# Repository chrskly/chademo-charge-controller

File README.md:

# CHAdeMO Implementation

This repo contains a car-side implementation of the CHAdeMO EV charging
standard including both the hardware and firmware.

## Features

* Supports CHAdeMO protocols v0.9, v1.0, and v2.0.
* Automatic sleep, wake on plug insertion.
* Separate manual wake button option.

## Chademo Plug Pinout

 1. Ground
 2. CP : evse => car, IN1, contactor +ve signal, goes high when active, sensed by 'f'
 3. nc
 4. CP3 : car => evse, OUT1, charge enable, sensed by 'k'
 5. HV-
 6. HV+
 7. CS : connection check, goes low when plug inserted, sensed by 'h'
 8. CAN H
 9. CAN L
10. CP2 : evse => car, IN2, contactor -ve signal, goes low when active, sensed by 'g'

OUT2, contactor override, pull low to allow CP2 signal through

## Charging start sequence

1. Car pulls CP high (12V) through R3 (1kΩ) when plug is inserted
2. User presses start button on station
3. Station pulls CP high (IN1), d1 closes, +ve contactor closes
4. Car and station start sending CAN messages
5. Car and station check each others params for compatability
6. Car pulls CP3 low and sets CAN vehicleChargingEnabled flag to true to
   indicate it is ready to go ahead with charging
7. Station locks plug to vehicle
8. Station performs insulation test
9. Station pulls CP2 low (IN2), d2 closes, -v3 contactor closes
10. Car ramps up current request. Energy transfer begins.

## Charging stop sequence

1. Car stops pulling CP3 low and sets CAN vehicleChargingEnabled to false.
2. Station deactivates CP and CP2
3. Station unlocks plug

## Questions

- [ ] When to use vehicleChargingEnabled and when to use vehicleRequestingStop?

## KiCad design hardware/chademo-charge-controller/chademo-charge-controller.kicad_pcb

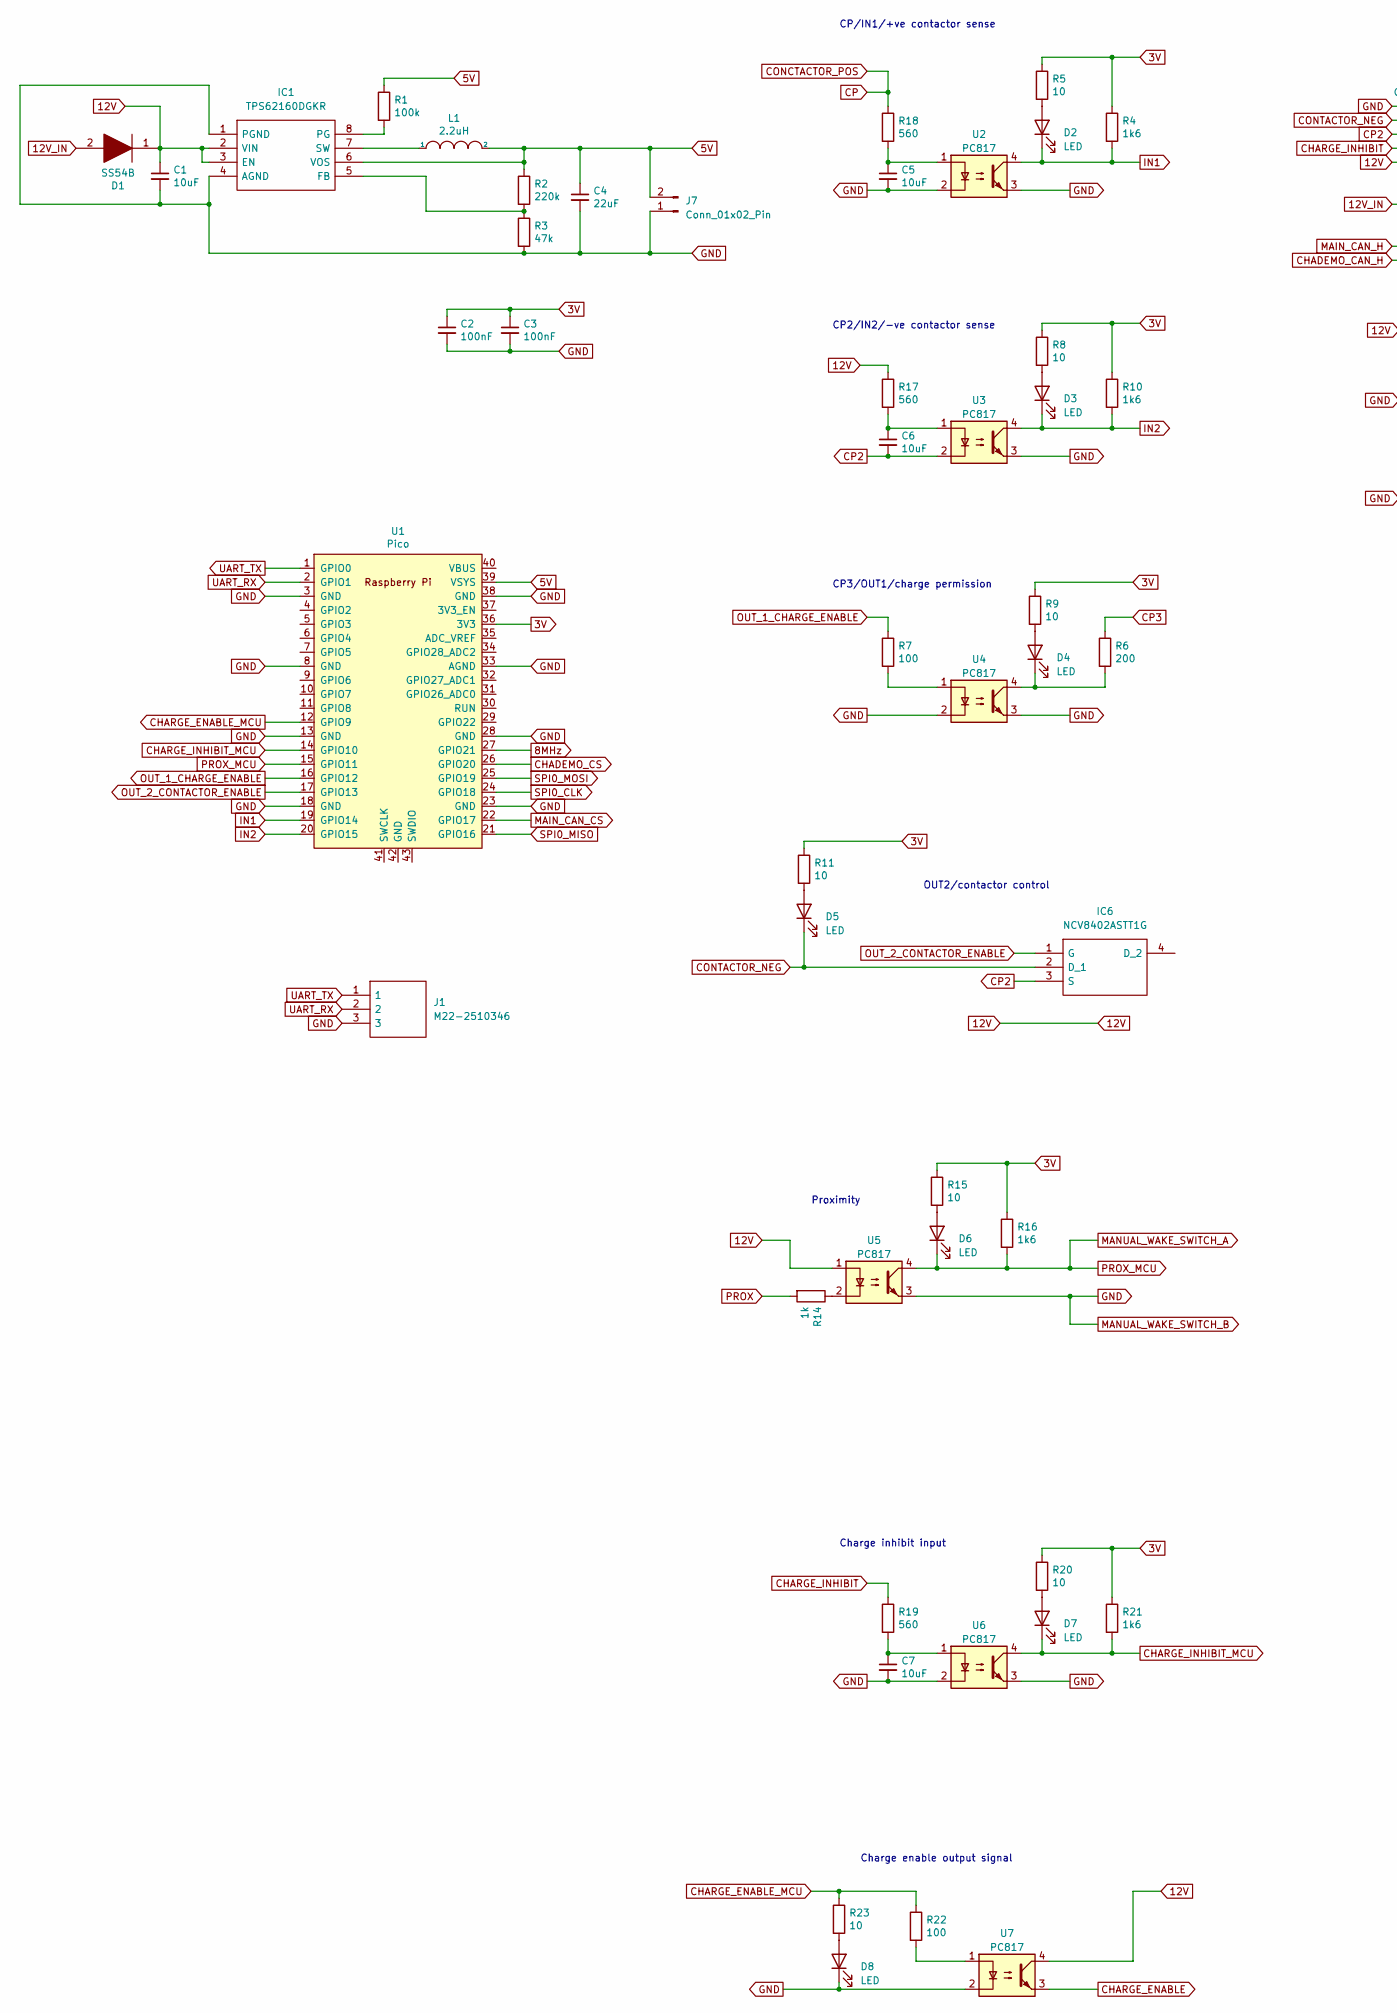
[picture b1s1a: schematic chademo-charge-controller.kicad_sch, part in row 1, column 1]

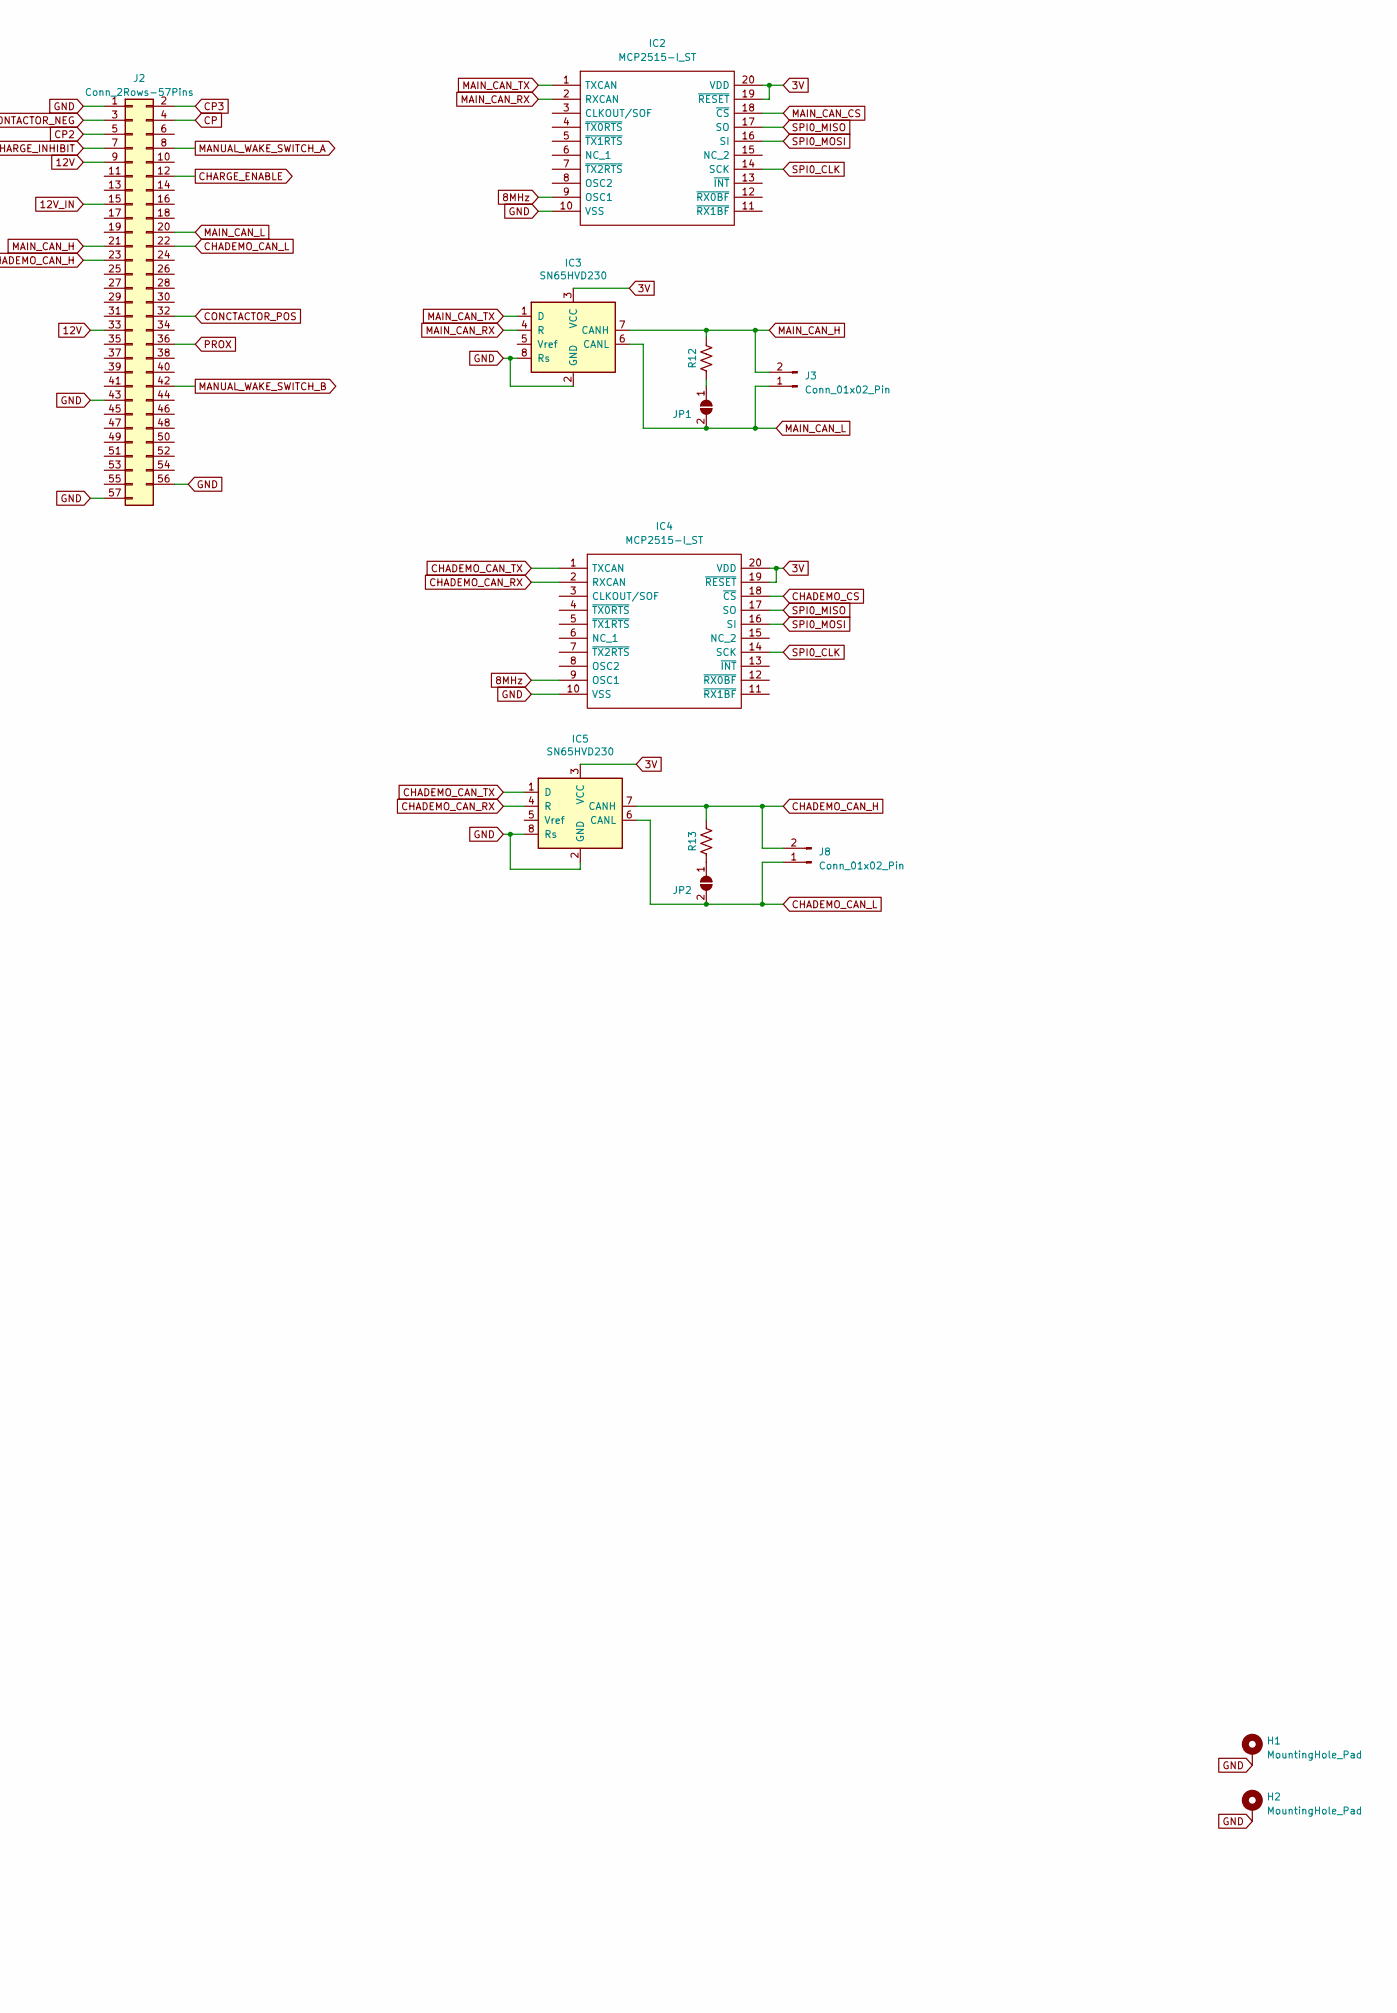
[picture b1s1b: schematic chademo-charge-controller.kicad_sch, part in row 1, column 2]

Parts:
C1, C5, C6, C7: 10uF; C_0603_1608Metric
C2, C3: 100nF; C_0603_1608Metric
C4: 22uF; C_0805_2012Metric
D1: SS54B; DIOM5336X244N; Manufacturer_Part_Number SS54B
D2, D3, D4, D5, D6, D7, D8: LED; LED_0805_2012Metric
H1, H2: MountingHole_Pad; MountingHole_3.2mm_M3_DIN965_Pad
IC1: TPS62160DGKR; SOP65P490X110-8N; Manufacturer_Part_Number TPS62160DGKR; Mouser Part Number 595-TPS62160DGKR
IC2, IC4: MCP2515-I_ST; SOP65P640X120-20N; Manufacturer_Part_Number MCP2515-I/ST
IC3, IC5: SN65HVD230; SOIC-8_3.9x4.9mm_P1.27mm
IC6: NCV8402ASTT1G; SOT230P700X175-4N; Manufacturer_Part_Number NCV8402ASTT1G; Mouser Part Number 863-NCV8402ASTT1G
J1: M22-2510346; PinHeader_1x03_P2.54mm_Horizontal; Manufacturer_Part_Number M22-2510346; Mouser Part Number 855-M22-2510346
J2: Conn_2Rows-57Pins; delphi56
J3, J7, J8: Conn_01x02_Pin; PinHeader_1x02_P2.54mm_Vertical
JP1, JP2: SolderJumper_2_Open; SolderJumper-2_P1.3mm_Open_Pad1.0x1.5mm
L1: 2.2uH; NR6028T220M
R1: 100k; R_0805_2012Metric
R2: 220k; R_0805_2012Metric
R3: 47k; R_0805_2012Metric
R4, R10, R16, R21: 1k6; R_0805_2012Metric
R5, R8, R9, R11, R15, R20, R23: 10; R_0805_2012Metric
R6: 200; R_0805_2012Metric
R7, R22: 100; R_0805_2012Metric
R12, R13: 120; R_0805_2012Metric
R14: 1k; R_0805_2012Metric
R17, R18, R19: 560; R_0805_2012Metric
U1: Pico; RPi_Pico_SMD_TH
U2, U3, U4, U5, U6, U7: PC817; DIP-4_W7.62mm

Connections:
3V: C2.1, C3.1, IC2.19 (~RESET), IC2.20 (VDD), IC3.3 (VCC), IC4.19 (~RESET), IC4.20 (VDD), IC5.3 (VCC), R4.1, R5.1, R8.1, R9.1, R10.1, R11.1, R15.1, R16.1, R20.1, R21.1, U1.36 (3V3)
5V: C4.1, IC1.6 (VOS), J7.2, L1.2, R1.1, R2.1, U1.39 (VSYS)
8MHz: IC2.9 (OSC1), IC4.9 (OSC1), U1.27 (GPIO21)
12V: C1.1, D1.1, IC1.2 (VIN), IC1.3 (EN), J2.9, J2.33, R17.1, U5.1, U7.4
12V_IN: D1.2, J2.15
CHADEMO_CAN_H: IC5.7 (CANH), J2.23, J8.2, R13.1
CHADEMO_CAN_L: IC5.6 (CANL), J2.22, J8.1, JP2.2 (B)
CHADEMO_CAN_RX: IC4.2 (RXCAN), IC5.4 (R)
CHADEMO_CAN_TX: IC4.1 (TXCAN), IC5.1 (D)
CHADEMO_CS: IC4.18 (~CS), U1.26 (GPIO20)
CHARGE_ENABLE: J2.12, U7.3
CHARGE_ENABLE_MCU: R22.1, R23.1, U1.12 (GPIO9)
CHARGE_INHIBIT: J2.7, R19.1
CHARGE_INHIBIT_MCU: D7.1 (K), R21.2, U1.14 (GPIO10), U6.4
CONCTACTOR_POS: J2.4, J2.32, R18.1
CONTACTOR_NEG: D5.1 (K), IC6.2 (D_1), J2.3
CP2: C6.2, IC6.3 (S), J2.5, U3.2
CP3: J2.2, R6.1
GND: C1.2, C2.2, C3.2, C4.2, C5.2, C7.2, D8.1 (K), H1.1, H2.1, IC1.1 (PGND), IC1.4 (AGND), IC2.10 (VSS), IC3.2 (GND), IC3.8 (Rs), IC4.10 (VSS), IC5.2 (GND), IC5.8 (Rs), J1.3, J2.1, J2.42, J2.43, J2.56, J2.57, J7.1, R3.2, U1.3 (GND), U1.8 (GND), U1.13 (GND), U1.18 (GND), U1.23 (GND), U1.28 (GND), U1.33 (AGND), U1.38 (GND), U2.2, U2.3, U3.3, U4.2, U4.3, U5.3, U6.2, U6.3, U7.2
IN1: D2.1 (K), R4.2, U1.19 (GPIO14), U2.4
IN2: D3.1 (K), R10.2, U1.20 (GPIO15), U3.4
MAIN_CAN_CS: IC2.18 (~CS), U1.22 (GPIO17)
MAIN_CAN_H: IC3.7 (CANH), J2.21, J3.2, R12.1
MAIN_CAN_L: IC3.6 (CANL), J2.20, J3.1, JP1.2 (B)
MAIN_CAN_RX: IC2.2 (RXCAN), IC3.4 (R)
MAIN_CAN_TX: IC2.1 (TXCAN), IC3.1 (D)
MANUAL_WAKE_SWITCH_A: D6.1 (K), J2.8, R16.2, U1.15 (GPIO11), U5.4
unnamed: C5.1, R18.2, U2.1
unnamed: C6.1, R17.2, U3.1
unnamed: C7.1, R19.2, U6.1
unnamed: D2.2 (A), R5.2
unnamed: D3.2 (A), R8.2
unnamed: D4.2 (A), R9.2
unnamed: D4.1 (K), R6.2, U4.4
unnamed: D5.2 (A), R11.2
unnamed: D6.2 (A), R15.2
unnamed: D7.2 (A), R20.2
unnamed: D8.2 (A), R23.2
unnamed: IC1.5 (FB), R2.2, R3.1
unnamed: IC1.8 (PG), R1.2
unnamed: IC1.7 (SW), L1.1
unnamed: JP1.1 (A), R12.2
unnamed: JP2.1 (A), R13.2
unnamed: R7.2, U4.1
unnamed: R14.1, U5.2
unnamed: R22.2, U7.1
OUT_1_CHARGE_ENABLE: R7.1, U1.16 (GPIO12)
OUT_2_CONTACTOR_ENABLE: IC6.1 (G), U1.17 (GPIO13)
PROX: J2.36, R14.2
SPI0_CLK: IC2.14 (SCK), IC4.14 (SCK), U1.24 (GPIO18)
SPI0_MISO: IC2.17 (SO), IC4.17 (SO), U1.21 (GPIO16)
SPI0_MOSI: IC2.16 (SI), IC4.16 (SI), U1.25 (GPIO19)
UART_RX: J1.2, U1.2 (GPIO1)
UART_TX: J1.1, U1.1 (GPIO0)

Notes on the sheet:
CP/IN1/+ve contactor sense
OUT2/contactor control
CP3/OUT1/charge permission
CP2/IN2/-ve contactor sense
Charge inhibit input
Charge enable output signal
Proximity

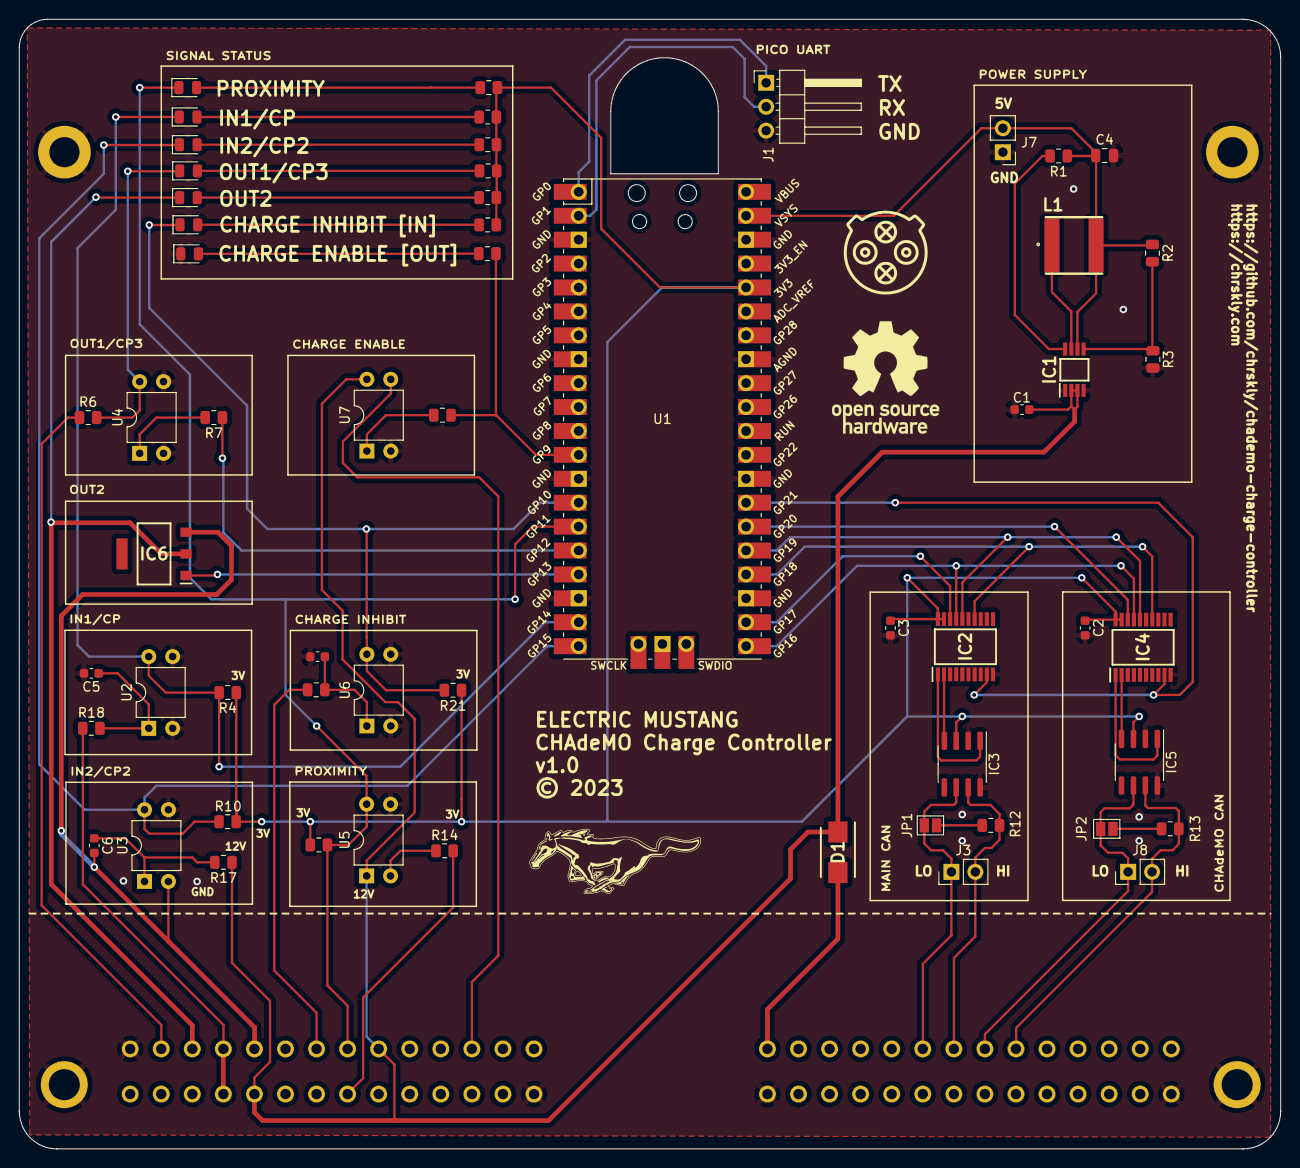
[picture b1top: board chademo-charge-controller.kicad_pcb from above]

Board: 2 copper layers, 134.0 x 120.0 mm, 61 parts (0 on the bottom side), 54 nets.

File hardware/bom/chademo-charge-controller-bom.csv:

Comment,Designator,Footprint,LCSC
TPS62160DGKR,IC1,MSOP-8,C60726
SS54,D1,SMB(DO-214AA),C880743
10uF,"C1,C5,C6,C7,",0805_C,C15850
2.2uH,L1,IND-SMD,C92941
100kΩ,R1,0805_R,C149504
220kΩ,R2,0805_R,C17539
47kΩ,R3,0805_R,C17713
22uF,C4,0805_C,C2835558
0.1uF,"C2,C3",0805_C,C49678
MCP2515-I/ST,"IC2,IC4",TSSOP-20,C15193
SN65HVD230,"IC3,IC5",SOIC-8,C12084
120Ω,"R12,R13",0805_R,C17437
560Ω,"R17,R18,R19",0805_R,C28636
10Ω,"R5,R8,R9,R11,R15,R20,R23",0805_R,C17415
1.6kΩ,"R4,R10,R16,R21",0805_R,C2930156
led,"D2,D3,D4,D5,D6,D7,D8",0805,C434432
200Ω,"R6",0805_R,C17540
1kΩ,"R14",0805_R,C17513
100Ω,"R7,R22",0805_R,C17408
PC817,"U2,U3,U4,U5,U6,U7",DIP-4,C3025067
NCV8402ASTT1G,"IC6",SOT223,C77755

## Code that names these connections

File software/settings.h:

/*
 * This file is part of the ev mustang charge controller project.
 *
 * Copyright (C) 2022 Christian Kelly <chrskly@chrskly.com>
 *
 * This program is free software: you can redistribute it and/or modify
 * it under the terms of the GNU General Public License as published by
 * the Free Software Foundation, either version 3 of the License, or
 * (at your option) any later version.
 *
 * This program is distributed in the hope that it will be useful,
 * but WITHOUT ANY WARRANTY; without even the implied warranty of
 * MERCHANTABILITY or FITNESS FOR A PARTICULAR PURPOSE.  See the
 * GNU General Public License for more details.
 *
 * You should have received a copy of the GNU General Public License
 * along with this program.  If not, see <http://www.gnu.org/licenses/>.
 */

#ifndef SETTINGS_H
#define SETTINGS_H

#define VERSION 1.0

// Serial port
#define UART_ID      uart0
#define BAUD_RATE   115200
#define UART_TX_PIN      0 // pin 1
#define UART_RX_PIN      1 // pin 2

// SPI
#define SPI_PORT      spi0
#define SPI_MISO        16 // pin 21
#define SPI_CLK         18 // pin 24
#define SPI_MOSI        19 // pin 25
#define CAN_CLK_PIN     21 // pin 27
#define MAIN_CAN_CS     17 // pin 22
#define CHADEMO_CAN_CS  20 // pin 26

// Inputs
#define PROX_PIN 11
#define CHADEMO_IN1_PIN 14  // pin 19, CP  - contactor +ve, (sensed by 'f'), d1 enable signal, chademo plug pin 2
#define CHADEMO_IN2_PIN 15  // pin 20, CP2 - contactor -ve, (sensed by 'g'), d2 enable signal, chademo plug pin 10
#define CHADEMO_CS_PIN 20   // pin 26, CS - pilot wire, input, (a.k.a 'h'), pilot signal, chademo plug pin 7

// Outputs
#define CHARGE_ENABLE_PIN 9     // pin 12
#define CHARGE_INHIBIT_PIN 10   // pin 14
#define CHADEMO_OUT1_PIN 12     // pin 16, CP3 - charge enable, (switched by 'k'), chademo plug pin 4
#define CHADEMO_OUT2_PIN 13     // pin 17, contactor relay control, 'e'
#define PICO_DEFAULT_LED_PIN 99 //


/*
 * General CHAdemMO settings
 */

/* Version of CHADeMO protocol that the vehicle will announce to the station
 * 0 == Before 0.9
 * 1 == v0.9 and v0.9.1
 * 2 == v1.0.0 and v1.0.1
 * 3 == v2.0.0 and v2.0.1
 */
#define CHADEMO_PROTOCOL_VERSION 1

// Messages from ChaDeMo station
#define EVSE_CAPABILITIES_MESSAGE_ID 0x108
#define EVSE_STATUS_MESSAGE_ID 0x109

// Spec says current requests from the car should only vary at a rate of +/- 20A/sec
#define CHADEMO_RAMP_RATE 20
#define CHADEMO_RAMP_INTERVAL 1000 // units = ms

// If we don't receive a CAN message from the ChaDeMo station in this number of
// seconds, then we must abort charging.
#define CHADEMO_STATION_TTL 2000 // units = ms

// This scaling factor is used to calculate max charging time from the estimated charging time
#define MAX_CHARGING_TIME_SCALING_FACTOR 1.2

/* Specify whether to use amp-hours (ah) or watt-hours (wh) to estimate how much
 * time is left to complete charging.
 */
#define CALCULATE_TIME_REMAINING_BASED_ON "ah"

/* The energy transfer stage is complete when the current drops below this value.
 */
#define TERMINATION_CURRENT 5

/* How long we wait for the contactors to open/close when we're doing weld
 * detection. If it takes longer than this, we consider the contactors welded.
 */
#define WELD_CHECK_TTL 1000 // units = ms


/*
 * General BMS settings
 */

// If we don't receive a CAN message from the BMS in this number of seconds,
// then we must abort charging.
#define BMS_TTL 5000 // units = ms

// BMS CAN message which contains max/min pack voltage, max dis/charge current
#define BMS_LIMITS_MESSAGE_ID 0x351

// BMS CAN messages which contains SoC
#define BMS_SOC_MESSAGE_ID 0x355

// BMS CAN message which contains pack voltage, current (not implemented), temp
#define BMS_STATUS_MESSAGE_ID 0x356

// BMS CAN message which contains alarms/warnings from BMS
#define BMS_ALARM_MESSAGE_ID 0x35A


/*
 * Battery settings
 */

// The SoC at which to stop fast-charging. Can be overriden via CAN msg.
#define BATTERY_FAST_CHARGE_DEFAULT_SOC_MAX 80

#define BATTERY_MAX_CURRENT 10          // fixme put in proper value
#define BATTERY_MAX_CURRENT_FAILSAFE 10 // maximum current to use if we lose communication with the BMS

// Stop charging when current drops to this level
#define TERMINATE_CHARGING_CURRENT 5

#endif

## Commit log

2023-07-17 Pull over code from other repo and strip out CCS stuff
2023-07-17 README
2023-07-19 Basic hardware layout
2023-07-20 pcb layout, 56pin socket
2023-07-28 tweaking hw
2023-08-06 lots of work on hardware
2023-09-19 I dunno ... lots
2023-09-26 get dhcp and basic http call working
2023-10-16 Add BMS liveness check
2023-10-16 rename fn
2023-10-16 Trigger events on CHAdeMO msg receipt
2023-10-16 Improvements to state machine
2023-10-16 New events
2023-10-16 comment
2023-10-16 terminate current setting
2023-10-16 Station liveness check
2023-10-16 whitespace
2023-10-16 termination conditions
2023-10-16 Docs update
2023-10-18 aux inhibit => idle/plug in
2023-10-18 missing prototype
2023-10-18 State machine work
2023-10-19 Rename some files
2023-10-19 Rename functions
2023-10-19 more renaming
2023-10-19 remove unused fn
2023-10-19 individual station status checks
2023-10-19 junk comment
2023-10-19 Documenting params received from station
2023-10-21 Tidy settings
2023-10-21 Use max voltage from bms rather than hardcoded value
2023-10-21 Fixing some parts of flow
2023-10-21 docs
2023-10-21 Get charge current limit straight from BMS
2023-10-21 don't need
2023-10-21 Add option to calculate time remaining based on ah or wh
2023-10-23 More work on flow
2023-10-24 CHAdeMO version spec
2023-10-24 Set maximumVoltage prior to vehicle permission and don't update after that
2023-10-24 Implement current deviation error logic
2023-10-27 Deal with more error states
2023-10-27 Fix string comparison
2023-10-27 clean
2023-10-27 Fix variable clash
2023-10-27 Fix string setting
2023-10-27 Probably not right, but it compiles for now
2023-10-27 tidy
2023-11-21 Very basic web server working
2023-11-21 remove old backup
2023-11-21 designing interface
2023-11-22 Get basic html serving successfully
2024-08-03 Working on web interface
2024-08-03 Fix voltage graph figures
2024-08-04 Add status/history/settings subtabs to battery tab
2024-08-04 Move web interface over to dashboard repo

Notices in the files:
hardware/chademo-charge-controller/chademo-charge-controller.kicad_pcb:
© 2023
